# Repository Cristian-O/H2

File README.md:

#### 2.4 GHz LoRa Gateway and Node for data aquisition powered by renewable energy

- Node

- Sensor modules

- Gateway

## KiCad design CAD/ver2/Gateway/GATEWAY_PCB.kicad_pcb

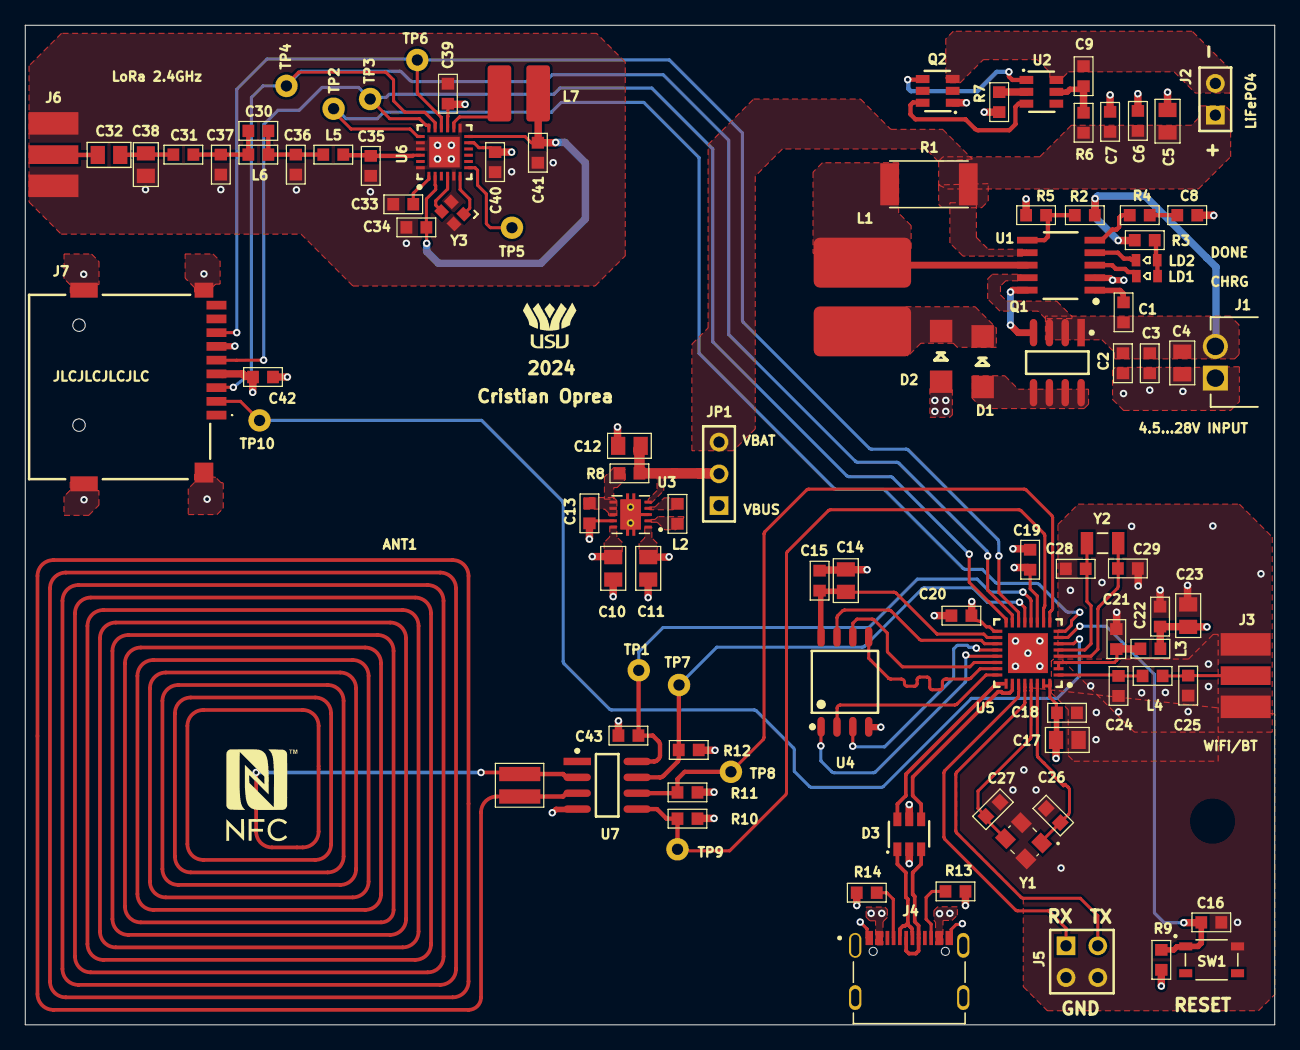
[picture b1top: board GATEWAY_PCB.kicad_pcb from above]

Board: 4 copper layers, 100.0 x 80.0 mm, 101 parts (0 on the bottom side), 70 nets.

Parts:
ANT1: NFC_ANTENNA; ANT16
C1, C2, C7, C9, C13, C14, C16, C18, C19, C20, C21, C22, C39, C40, C42, C43: 100nF; C0603
C3, C6: 4.7uF; C0603
C4, C5, C10, C11, C12, C15, C17, C23: 10uF; C0805
C8: 220nF; C0603
C24, C25: 3p3; C0603
C26, C27, C28, C29: 16pF; C0603
C30: 0.5pF; C0603
C31: 100pF; C0603
C32, C38: TBD; C0805
C33, C34: 10nF; C0603
C35: 0.8pF; C0603
C36, C37: 1.2pF; C0603
C41: 470nF; C0603
D1, D2: SS34; DO-214AC
D3: USBLC6-2SC6; SOT23-6
J1: PLUGIN_TERMINAL; 2.54_PLUGGABLE_TERMINAL
J2: PLUGIN_TERMINAL; HEADER_1X2_2.54
J3: SMA; CON_SMA-EDGE-S
J4: USB4145-03-0170-C; VALCON_CSP-USC16-TR
J5: Header1x4; HEADER_2X2_2.54
J6: SMA_EDGE_CONN; CON_SMA-EDGE-S
J7: uSD_CARD_HOLDER; TF115BCP9
JP1: JUMPER_3PIN; HEADER_1X3_2.54
L1: 47uH; IND_5_7
L2: 2.2uH; L0603
L3, L4: 2.2nH; L0603
L5: 3nH; L0603
L6: 2.5nH; L0603
L7: 15uH; IND_3.2_4
LD1: LED_RED; LED0603RD
LD2: LED_GREEN; LED0603GR
Q1: FDS4435; SOIC-SN8_N
Q2: FS8205; SOT23-6
R1: 0R250; R2512
R2: 27k; R0603
R3: 1k5; R0603
R4: 120R; R0603
R5: 3k; R0603
R6, R8: 100R; R0603
R7: 2k; R0603
R9, R10, R11, R12, R13, R14: 5.1k; R0603
SW1: PTS645SM43SMTR92 LFS; SW_SKRPACE010
TP1, TP2, TP3, TP4, TP5, TP6, TP7, TP8, TP9, TP10: TP_NOBOM; TEST_PAD_THD
U1: CN3801; SSOP-10
U2: HY2112; SOT23-6
U3: TPS63000; VREG_V62/16624-01YE
U4: W25Q16JVUXIQ; SOIC-8N_208mil
U5: ESP32-C3; QFN-32-5X5X0.85MM
U6: SX1280; QFN-24_4X4_0.5
U7: ST25DV04K; SOIC-SN8_N
Y1: 40 MHz; CRYSTAL_ECX-32_3.2X2.5X0.8 - DUPLICATE
Y2: 32.768kHz; CRYSTAL_SX-3215
Y3: 52MHz; CRYSTAL_2016_4P

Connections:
3V3: C10.2, C11.2, C17.2, C18.2, C19.2, C20.2, C22.2, C23.2, C39.2, C40.2, C42.2, J7.4, L3.2, R9.2, R10.2, R11.2, R12.2, U3.1, U3.10, U5.11, U5.17, U5.31, U5.32, U6.11, U6.15
3V3_RF: C21.2, L3.1, U5.2, U5.3
CHIP_EN: C16.2, R9.1, SW1.1, U5.7
GND: C2.1, C3.1, C4.1, C5.1, C6.1, C7.1, C8.1, C10.1, C11.1, C12.1, C13.1, C14.1, C15.1, C16.1, C17.1, C18.1, C19.1, C20.1, C21.1, C22.1, C23.1, C24.1, C25.1, C26.1, C27.1, C28.1, C29.1, C33.1, C34.1, C35.1, C36.1, C37.1, C38.1, C39.1, C40.1, C41.1, C42.1, C43.1, D2.1, D3.2, J1.1, J3.2, J4.A1, J4.A12, J4.B1, J4.B12, J5.3, J5.4, J6.2, J7.6, J7.10, J7.11, J7.12, J7.13, Q2.1, R5.1, R7.1, R13.1, R14.1, SW1.2, U1.2, U3.3, U3.9, U3.11, U4.4, U5.33, U6.5, U6.13, U6.20, U6.21, U6.24, U6.25, U7.4, Y1.2, Y1.4, Y3.2, Y3.4
MCU_USB_D_N: D3.6, U5.25
MCU_USB_D_P: D3.4, U5.26
NetANT1_1: ANT1.1, U7.2
NetANT1_2: ANT1.2, U7.3
NetC1_1: C1.1, U1.1
NetC8_2: C8.2, R4.1
NetC9_2: C9.2, R6.2, U2.5
NetC12_2: C12.2, JP1.2, R8.2, U3.5
NetC13_2: C13.2, R8.1, U3.6, U3.7, U3.8
NetC24_2: C24.2, L4.1, U5.1
NetC25_2: C25.2, J3.1, L4.2
NetC26_2: C26.2, U5.30, Y1.1
NetC27_2: C27.2, U5.29, Y1.3
NetC28_2: C28.2, U5.5, Y2.2
NetC29_2: C29.2, U5.4, Y2.1
NetC30_1: C30.1, C31.2, C37.2, L6.2
NetC30_2: C30.2, C36.2, L5.2, L6.1
NetC31_1: C31.1, C32.2, C38.2
NetC32_1: C32.1, J6.1
NetC33_2: C33.2, U6.1
NetC34_2: C34.2, C41.2, L7.1, U6.2, U6.12
NetC35_2: C35.2, L5.1, U6.22
NetC43_2: C43.2, TP1.1, U5.12, U7.8
NetD1_1: D1.1, Q1.5, Q1.6, Q1.7, Q1.8
NetD1_2: D1.2, D2.2, L1.1
NetJ4_A5: J4.A5, R14.2
NetJ4_B5: J4.B5, R13.2
NetJ7_2: J7.2, TP10.1, U5.6
NetJ7_3: J7.3, TP4.1, U5.15, U6.17
NetJ7_5: J7.5, TP3.1, U5.16, U6.18
NetJ7_7: J7.7, TP6.1, U5.14, U6.16
NetL1_2: L1.2, R1.1, U1.8
NetL2_1: L2.1, U3.4
NetL2_2: L2.2, U3.2
NetL7_2: L7.2, U6.14
NetLD1_1: LD1.1, LD2.1, R3.1
NetLD1_2: LD1.2, U1.3
NetLD2_2: LD2.2, U1.4
NetQ1_4: Q1.4, U1.10
NetQ2_4: Q2.4, U2.1
NetQ2_6: Q2.6, U2.3
NetR2_1: R2.1, R5.2, U1.6
NetR4_2: R4.2, U1.5
NetR7_2: R7.2, U2.2
NetR10_1: R10.1, TP9.1, U5.10, U7.5
NetR11_1: R11.1, TP8.1, U5.9, U7.6
NetR12_1: R12.1, TP7.1, U5.13, U7.7
NetTP2_1: TP2.1, U5.8, U6.19
NetTP5_1: TP5.1, U6.7
NetU6_4: U6.4, Y3.3
NetU6_6: U6.6, Y3.1
SPI_CLK: U4.6, U5.22
SPI_DI: U4.5, U5.23
SPI_DO: U4.2, U5.24
SPI_NCS: U4.1, U5.21
SPI_NHOLD: U4.7, U5.19
SPI_NWP: U4.3, U5.20
UART0_RXD: J5.1, U5.27
UART0_TXD: J5.2, U5.28
USB_D_N: D3.1, J4.A7, J4.B7
USB_D_P: D3.3, J4.A6, J4.B6
VBAT+: C5.2, C6.2, C7.2, J2.1, JP1.3, R1.2, R6.1, U1.7
VBAT-: C9.1, J2.2, Q2.3, U2.6
VBUS: D3.5, J4.A4, J4.A9, J4.B4, J4.B9, JP1.1
VDD_SPI: C14.2, C15.2, U4.8, U5.18
VIN: C1.2, C2.2, C3.2, C4.2, J1.2, Q1.1, Q1.2, Q1.3, R2.2, R3.2, U1.9

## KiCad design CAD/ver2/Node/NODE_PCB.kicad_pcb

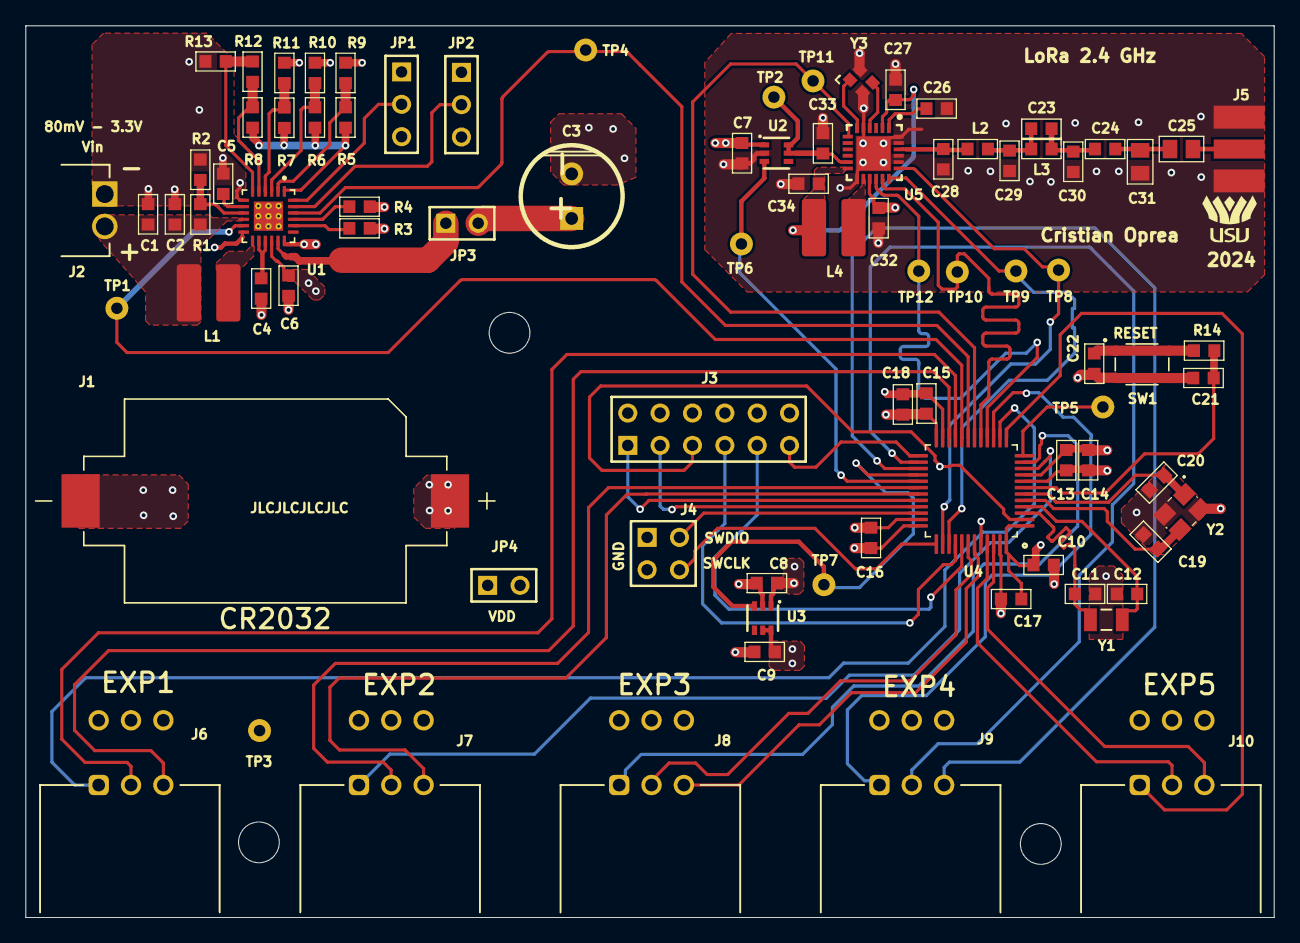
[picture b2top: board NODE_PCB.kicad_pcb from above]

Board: 4 copper layers, 98.0 x 70.0 mm, 87 parts (0 on the bottom side), 72 nets.

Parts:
C1, C4: 10uF; C0603
C2, C9, C10, C15, C16, C17, C32, C33: 100nF; C0603
C3: Supercapacitor; CAP_POL_8X16X3.5
C5, C13, C21, C26, C27: 10nF; C0603
C6, C18: 4.7uF; C0603
C7, C8, C14: 1uF; C0603
C11, C12, C19, C20, C22: 16pF; C0603
C23: 0.5pF; C0603
C24: 100pF; C0603
C25, C31: TBD; C0805
C28: 0.8pF; C0603
C29, C30: 1.2pF; C0603
C34: 470nF; C0603
J1: CR2032; BAT_CR2032-BS-6-1
J2: Plugin Terminal; 2.54_PLUGGABLE_TERMINAL
J3: Header 6X2; HEADER_6X2_2.54
J4: SWD connector; HEADER_2X2_2.54
J5: SMA_EDGE_CONN; CON_SMA-EDGE-S
J6, J7, J8, J9, J10: EDGE_CONNECTOR; 2.54MM_EDGE_CONNECTOR
JP1, JP2: JUMPER_3PIN; HEADER_1x3_2.54
JP3, JP4: JUMPER; HEADER_1X2_2.54
L1: 22uH; IND_3.2_4
L2: 3nH; R0603
L3: 2.5nH; R0603
L4: 15uH; IND_3.2_4
R1: 4.7M; R0603
R2: 18M; R0603
R3: 221k; R0603
R4: 150k; R0603
R5: 5.49M; R0603
R6, R8: 5.9M; R0603
R7: 6.04M; R0603
R9: 4.53M; R0603
R10, R13: 4.12M; R0603
R11: 3.92M; R0603
R12: 100k; R0603
R14: 1.5k; R0603
SW1: PTS645SM43SMTR92 LFS; SW_SKRPACE010
TP1, TP2, TP3, TP4, TP5, TP6, TP7, TP8, TP9, TP10, TP11, TP12: TP_NOBOM; TEST_PAD_THD
U1: ADP5091; LFCSP-24
U2, U3: TPS22919; SC70-6
U4: STM32L431; QFPN-48
U5: SX1280; QFN-24_4X4_0.5
Y1: 32.768kHz; CRYSTAL_SX-3215
Y2: 8MHz; CRYSTAL_ECX-32_3.2X2.5X0.8 - DUPLICATE
Y3: 52MHz; CRYSTAL_2016_4P

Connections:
GND: C1.1, C2.1, C3.2, C4.2, C5.1, C6.1, C7.1, C8.1, C9.1, C10.1, C11.1, C12.1, C13.1, C14.1, C15.1, C16.1, C17.1, C18.1, C19.1, C20.1, C21.1, C22.1, C26.1, C27.1, C28.1, C29.1, C30.1, C31.1, C32.1, C33.1, C34.1, J1.N, J2.1, J3.2, J3.4, J3.6, J3.8, J3.10, J3.12, J4.1, J4.3, J5.2, J6.5, J6.6, J7.5, J7.6, J8.5, J8.6, J9.5, J9.6, J10.5, J10.6, JP1.3, JP2.3, R2.1, R3.1, R4.1, R9.1, R10.1, R11.1, R13.1, SW1.3, SW1.4, U1.7, U1.12, U2.2, U3.2, U4.8, U4.23, U4.35, U4.44, U4.47, U5.5, U5.13, U5.20, U5.21, U5.23, U5.24, U5.25, Y2.2, Y2.4, Y3.2, Y3.4
NetC3_1: C3.1, JP3.2
NetC4_1: C4.1, U1.14, U1.15
NetC5_2: C5.2, U1.8
NetC6_2: C6.2, JP4.1, U1.16
NetC11_2: C11.2, U4.3, Y1.2
NetC12_2: C12.2, U4.4, Y1.1
NetC19_2: C19.2, U4.5, Y2.3
NetC20_2: C20.2, U4.6, Y2.1
NetC21_2: C21.2, R14.1, U4.7
NetC22_2: C22.2, R14.2, SW1.1, SW1.2
NetC23_1: C23.1, C24.2, C30.2, L3.2
NetC23_2: C23.2, C29.2, L2.2, L3.1
NetC24_1: C24.1, C25.2, C31.2
NetC25_1: C25.1, J5.1
NetC26_2: C26.2, U5.1
NetC27_2: C27.2, C34.2, L4.1, U5.2, U5.12
NetC28_2: C28.2, L2.1, U5.22
NetJ1_P: J1.P, U1.18
NetJ6_1: J6.1, U4.14
NetJ6_2: J6.2, U4.21
NetJ6_3: J6.3, U4.22
NetJ7_1: J7.1, U4.10
NetJ7_2: J7.2, U4.30
NetJ7_3: J7.3, U4.31
NetJ8_1: J8.1, U4.11
NetJ8_2: J8.2, U4.42
NetJ8_3: J8.3, U4.43
NetJ9_1: J9.1, U4.15
NetJ9_2: J9.2, U4.26
NetJ9_3: J9.3, U4.27
NetJ10_1: J10.1, U4.13
NetJ10_2: J10.2, U4.45
NetJ10_3: J10.3, U4.46
NetJP3_1: JP3.1, U1.17
NetL1_1: L1.1, U1.13
NetL4_2: L4.2, U5.14
NetR1_1: R1.1, R2.2, U1.9
NetR3_2: R3.2, U1.20
NetR4_2: R4.2, U1.21
NetR5_1: R5.1, R9.2, U1.2
NetR5_2: R5.2, R6.2, R7.2, R8.2, U1.1
NetR6_1: R6.1, R10.2, U1.3
NetR7_1: R7.1, R11.2, U1.4
NetR8_1: R8.1, R12.2, U1.5
NetR12_1: R12.1, R13.2, U1.6
NetTP1_1: TP1.1, U1.11, U4.20
NetTP4_1: TP4.1, U1.22, U4.19
NetTP6_1: TP6.1, U2.3, U4.29
NetTP7_1: TP7.1, U3.3, U4.28
NetTP8_1: TP8.1, U4.38, U5.19
NetTP9_1: TP9.1, U4.39, U5.18
NetTP10_1: TP10.1, U4.17, U5.17
NetTP11_1: TP11.1, U4.18, U5.7
NetTP12_1: TP12.1, U4.16, U5.16
NetU5_4: U5.4, Y3.3
NetU5_6: U5.6, Y3.1
PA11: J3.1, U4.32
PA12: J3.3, U4.33
PB4: J3.7, U4.40
PB5: J3.9, U4.41
PB12: J3.11, U4.25
PC13: J3.5, U4.2
REG_D0: JP1.2, U1.24
REG_D1: JP2.2, U1.23
SWCLK: J4.4, U4.37
SWDIO: J4.2, U4.34
UART_TX: TP5.1, U4.12
VDD: C7.2, C8.2, C10.2, C13.2, C14.2, C15.2, C16.2, C17.2, C18.2, JP1.1, JP2.1, JP4.2, U2.1, U3.1, U4.1, U4.9, U4.24, U4.36, U4.48
VDD_COM: C32.2, C33.2, TP2.1, U2.5, U2.6, U5.11, U5.15
VDD_SENS: C9.2, J6.4, J7.4, J8.4, J9.4, J10.4, TP3.1, U3.5, U3.6
VIN: C1.2, C2.2, J2.2, L1.2, R1.2, U1.10

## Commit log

2023-11-08 Create Gateway
    Gateway PCB
2023-11-08 Create test
2023-11-09 Create Enclosure
2023-11-20 Create Gateway_info
2023-11-20 Rename Gateway_info to Gateway_info.md
2023-12-01 Create links
2023-12-01 Update links
2023-12-05 Added production files in .rar format
    Ready for ordering
2023-12-14 Update test
2023-12-14 Create versions
2024-01-08 Create app development folder
    App development using react native and expo mainly for android devices (easier implementation for NFC and BLE)
2024-01-08 App version 1
    Version 1 contains: menu system( each page has its own .js file), graph representation via web view, splash screen and app icon
2024-01-08 Create Monopole antenna
2024-01-08 Create Monopole
2024-01-22 Rename BOM_ALL.xlsx to BOM.xlsx
2024-01-22 Rename Node_test.md to Node_expansion_test.md
2024-04-07 Create Node_expansion_test
2024-04-07 Rename Node_expansion_test to Node_expansion_test.md
2024-06-30 Create ver1
